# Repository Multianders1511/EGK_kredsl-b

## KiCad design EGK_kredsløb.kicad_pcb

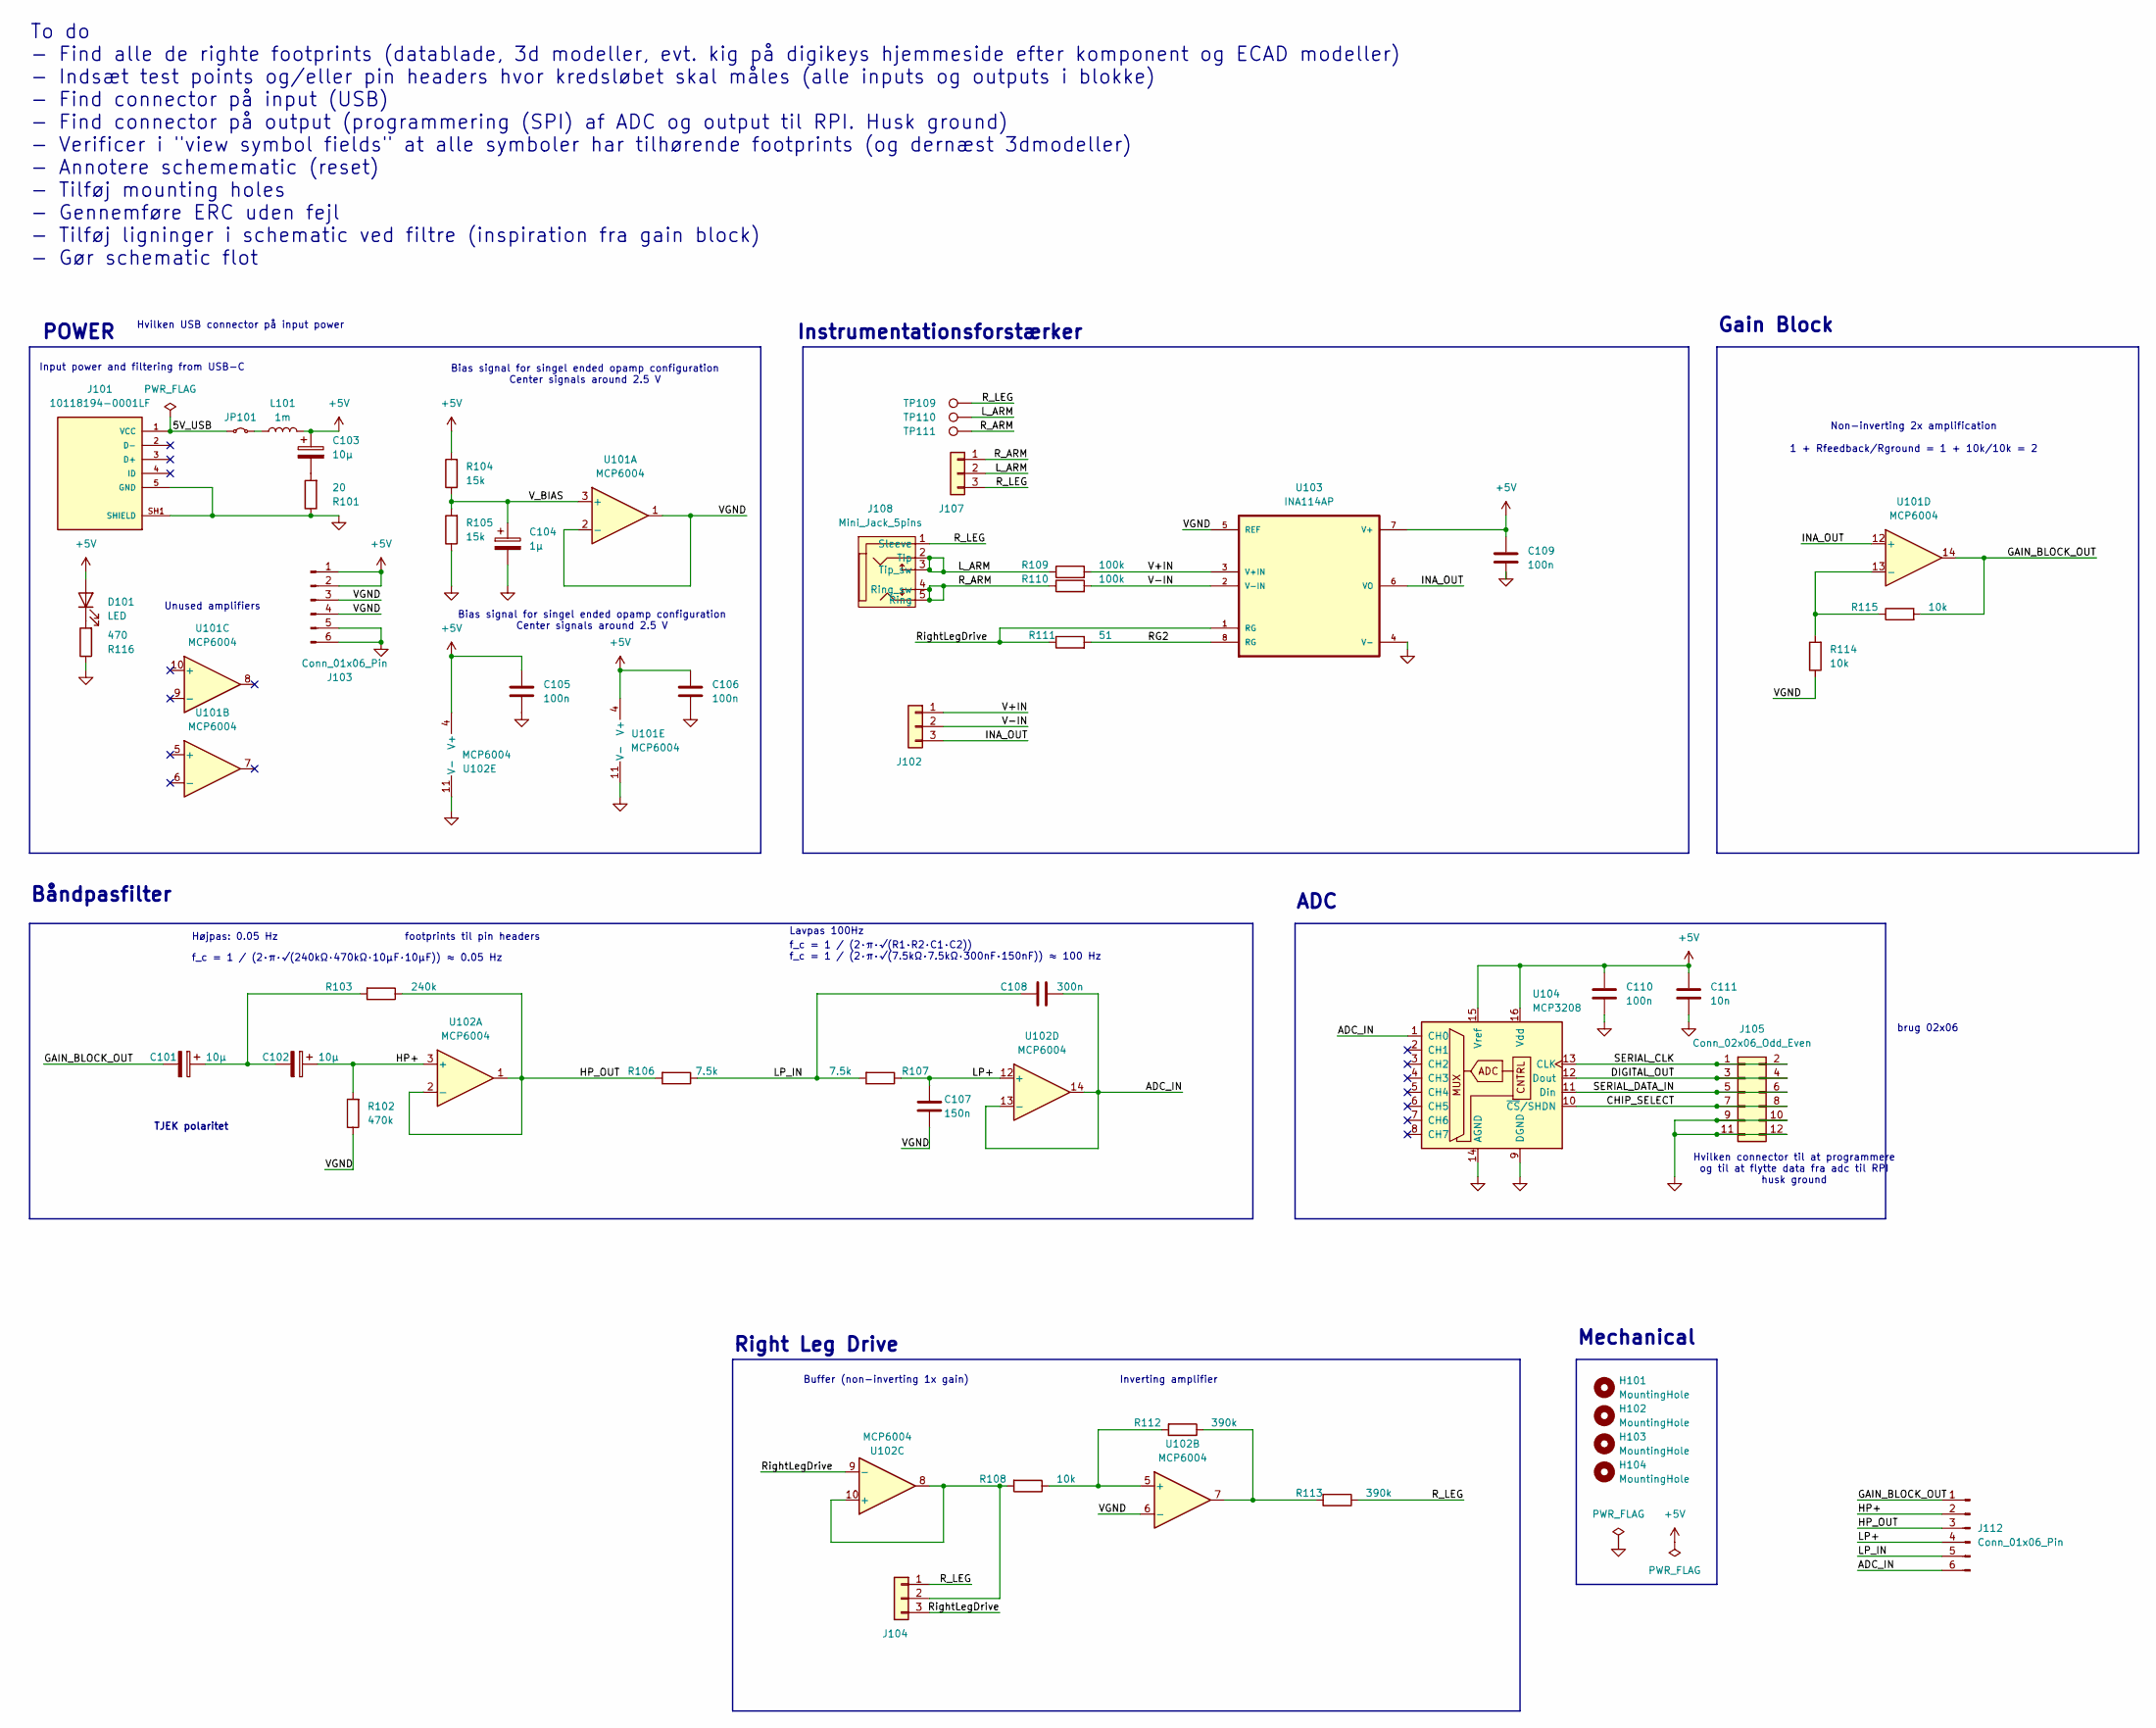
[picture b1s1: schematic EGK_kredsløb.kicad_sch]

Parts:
C101, C102, C103: 10μ; CP_Radial_D6.3mm_P2.50mm
C104: 1μ; CP_Radial_D6.3mm_P2.50mm
C105, C106, C109, C110: 100n; C_Rect_L7.0mm_W2.0mm_P5.00mm
C107: 150n; C_Rect_L7.0mm_W2.0mm_P5.00mm
C108: 300n; C_Rect_L7.0mm_W2.0mm_P5.00mm
C111: 10n; C_Rect_L7.0mm_W2.0mm_P5.00mm
D101: LED; LED_D5.0mm
H101, H102, H103, H104: MountingHole; MountingHole_3.2mm_M3_ISO7380
J101: 10118194-0001LF; AMPHENOL_10118194-0001LF; PARTREV D
J102, J104, J107: Conn_01x03; PinHeader_1x03_P2.54mm_Vertical
J103, J112: Conn_01x06_Pin; PinHeader_1x06_P2.54mm_Vertical
J105: Conn_02x06_Odd_Even; PinHeader_2x06_P2.54mm_Vertical
J108: Mini_Jack_5pins; mini_jack_5pins
JP101: Jumper_2_Small_Bridged; PinHeader_1x02_P2.54mm_Vertical
L101: 1m; L_Axial_L7.0mm_D3.3mm_P12.70mm_Horizontal_Fastron_MICC
R101: 20; R_Axial_DIN0207_L6.3mm_D2.5mm_P10.16mm_Horizontal
R102: 470k; R_Axial_DIN0207_L6.3mm_D2.5mm_P10.16mm_Horizontal
R103: 240k; R_Axial_DIN0207_L6.3mm_D2.5mm_P10.16mm_Horizontal
R104, R105: 15k; R_Axial_DIN0207_L6.3mm_D2.5mm_P10.16mm_Horizontal
R106, R107: 7.5k; R_Axial_DIN0207_L6.3mm_D2.5mm_P10.16mm_Horizontal
R108, R114, R115: 10k; R_Axial_DIN0207_L6.3mm_D2.5mm_P10.16mm_Horizontal
R109, R110: 100k; R_Axial_DIN0207_L6.3mm_D2.5mm_P10.16mm_Horizontal
R111: 51; R_Axial_DIN0207_L6.3mm_D2.5mm_P10.16mm_Horizontal
R112, R113: 390k; R_Axial_DIN0207_L6.3mm_D2.5mm_P10.16mm_Horizontal
R116: 470; R_Axial_DIN0207_L6.3mm_D2.5mm_P10.16mm_Horizontal
TP109, TP110, TP111: TestPoint; TestPoint_Pad_D3.0mm
U101, U102: MCP6004; DIP-14_W7.62mm_Socket_LongPads
U103: INA114AP; PDIP8; LCSC C38890
U104: MCP3208; DIP-16_W7.62mm_Socket_LongPads

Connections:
+5V: C103.1, C105.1, C106.1, C109.1, C110.1, C111.1, D101.2 (A), J103.1, J103.2, L101.2, R104.2, U101.4 (V+), U102.4 (V+), U103.7 (V+), U104.15 (Vref), U104.16 (Vdd)
/5V_USB: J101.1 (VCC), JP101.1 (A)
/ADC_IN: C108.2, J112.6, U102.13 (-), U102.14, U104.1 (CH0)
/CHIP_SELECT: J105.7, J105.8, U104.10 (~CS/SHDN)
/DIGITAL_OUT: J105.3, J105.4, U104.12 (Dout)
/GAIN_BLOCK_OUT: C101.2, J112.1, R115.2, U101.14
/HP+: C102.1, J112.2, R102.2, U102.3 (+)
/HP_OUT: J112.3, R103.1, R106.2, U102.1, U102.2 (-)
/INA_OUT: J102.3, U101.12 (+), U103.6 (VO)
/LP+: C107.2, J112.4, R107.1, U102.12 (+)
/LP_IN: C108.1, J112.5, R106.1, R107.2
/L_ARM: J107.2, J108.2 (Tip), J108.3 (Tip_sw), R109.1, TP110.1
/RG2: R111.2, U103.8 (RG)
/R_ARM: J107.1, J108.4 (Ring_sw), J108.5 (Ring), R110.1, TP111.1
/R_LEG: J104.1, J107.3, J108.1 (Sleeve), R113.1, TP109.1
/RightLegDrive: J104.3, R111.1, U102.9 (-), U103.1 (RG)
/SERIAL_CLK: J105.1, J105.2, U104.13 (CLK)
/SERIAL_DATA_IN: J105.5, J105.6, U104.11 (Din)
/V+IN: J102.1, R109.2, U103.3 (V+IN)
/V-IN: J102.2, R110.2, U103.2 (V-IN)
/VGND: C107.1, J103.3, J103.4, R102.1, R114.1, U101.1, U101.2 (-), U102.6 (-), U103.5 (REF)
/V_BIAS: C104.1, R104.1, R105.2, U101.3 (+)
GND: C104.2, C105.2, C106.2, C109.2, C110.2, C111.2, J101.5 (GND), J101.SH1 (SHIELD), J101.SH2 (SHIELD), J101.SH3 (SHIELD), J101.SH4 (SHIELD), J101.SH5 (SHIELD), J101.SH6 (SHIELD), J103.5, J103.6, J105.9, J105.10, J105.11, J105.12, R101.1, R105.1, R116.1, U101.11 (V-), U102.11 (V-), U103.4 (V-), U104.9 (DGND), U104.14 (AGND)
unnamed: C101.1, C102.2, R103.2
unnamed: C103.2, R101.2
unnamed: D101.1 (K), R116.2
unnamed: J104.2, R108.2, U102.8, U102.10 (+)
unnamed: JP101.2 (B), L101.1
unnamed: R112.1, R113.2, U102.7
unnamed: R114.2, R115.1, U101.13 (-)
unnamed: R108.1, R112.2, U102.5 (+)

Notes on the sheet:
Input power and filtering from USB-C
brug 02x06
footprints til pin headers
Gain Block
Buffer (non-inverting 1x gain)
Inverting amplifier
Non-inverting 2x amplification 1 + Rfeedback/Rground = 1 + 10k/10k = 2
Båndpasfilter
To do - Find alle de righte footprints (datablade, 3d modeller, evt. kig på digikeys hjemmeside efter komponent og ECAD modeller) - Indsæt test points og/eller pin headers hvor kredsløbet skal måles (alle inputs og outputs i blokke) - Find connector på input (USB) - Find connector på output (progra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
Bias signal for singel ended opamp configuration Center signals around 2.5 V
TJEK polaritet
Instrumentationsforstærker
Mechanical
f_c = 1 / (2·π·√(240kΩ·470kΩ·10µF·10µF)) ≈ 0.05 Hz
Right Leg Drive
Lavpas 100Hz
f_c = 1 / (2·π·√(R1·R2·C1·C2)) f_c = 1 / (2·π·√(7.5kΩ·7.5kΩ·300nF·150nF)) ≈ 100 Hz
Hvilken USB connector på input power
Højpas: 0.05 Hz
POWER
ADC
Hvilken connector til at programmere og til at flytte data fra adc til RPI husk ground
Unused amplifiers

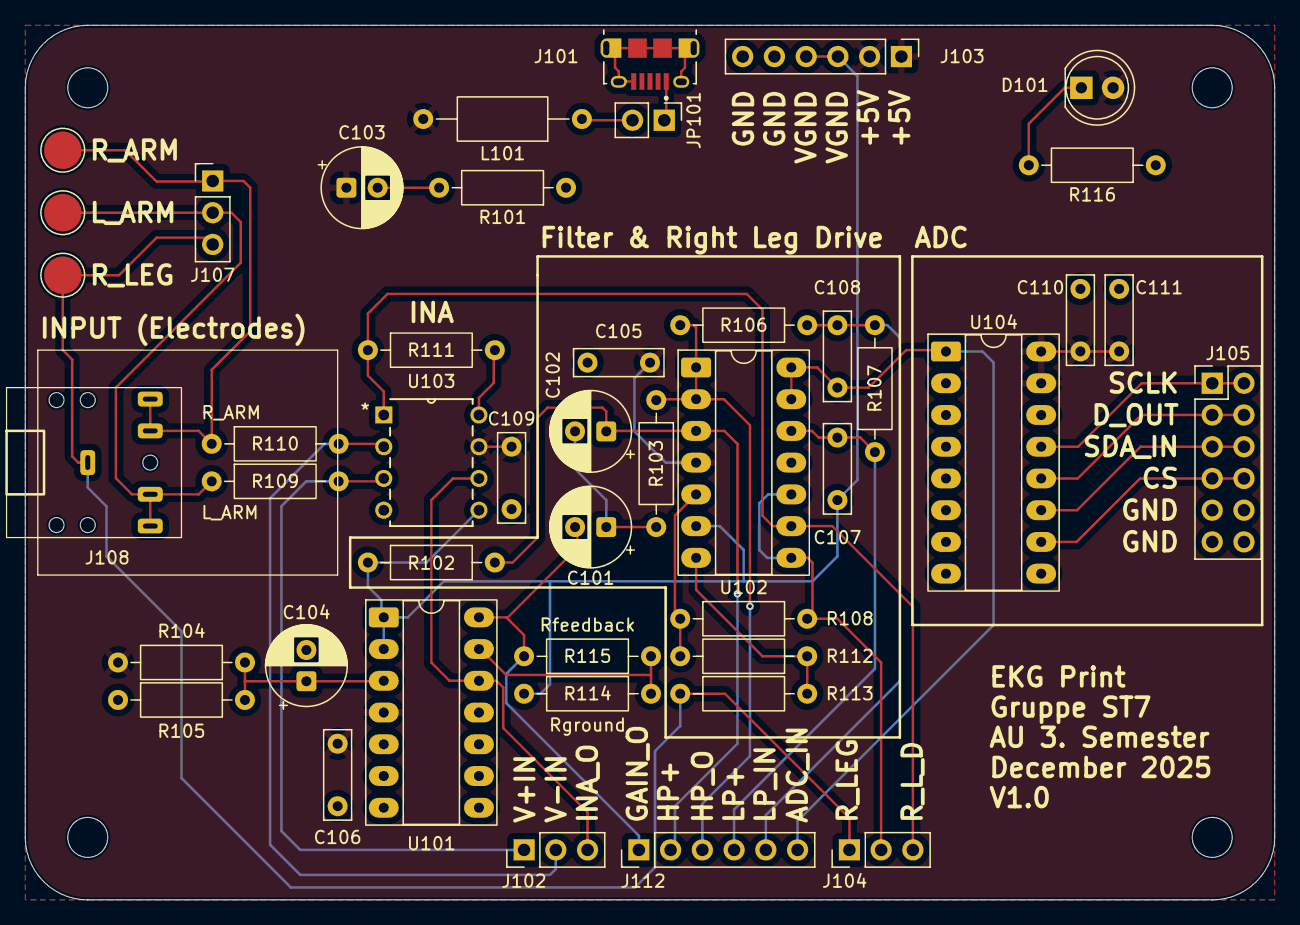
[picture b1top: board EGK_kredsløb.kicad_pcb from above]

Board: 2 copper layers, 100.0 x 70.0 mm, 49 parts (0 on the bottom side), 31 nets.

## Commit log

2025-11-14 finished schematic, missing AUX
2025-11-18 opdateret med micro-usb samt 3.5mm audio jack til elektroder
2025-11-18 ERC tjek, labels tilføjet til mini jack
2025-11-18 Add test.txt with initial content
2025-11-18 added test2.txt
2025-11-18 Add layout floorplan ready for routing
2025-11-18 3d-model til usb
2025-11-19 opstart af routing
2025-11-19 små ændringer med routing igen
2025-11-19 routed pcb
